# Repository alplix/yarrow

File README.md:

# Yarrow

Open software for Geiger counters: firmware for the FNIRSI GC-03, a BOINC monitor that reads several kinds of counters, and
a desktop app. Together they feed a live, open map of the natural background dose rate, city by city.

**Website:** [yarrow.athena.org.tr](https://yarrow.athena.org.tr) · **Live map:** [bitboinc.athena.org.tr/yarrow.php](https://bitboinc.athena.org.tr/yarrow.php) · **Data by city:** [bitboinc.athena.org.tr/yarrow_history.php](https://bitboinc.athena.org.tr/yarrow_history.php) · **Releases:** [firmware per language and Yarrow Hub](https://github.com/alplix/yarrow/releases)

3D Printed Dock: https://www.crealitycloud.com/tr/model-detail/6adf8eee3737a58cb2d2e141?profileId=6adf8eee3737a58cb2d2e147

## The parts

| | |
|---|---|
| **Firmware** (`src/`) | Open firmware for the FNIRSI GC-03: readable at a glance, measures honestly, logs for years. |
| **BOINC monitor** (`monitor/`) | A small program that reads a counter, cuts its pulses into exact 10-minute bins and sends them to the project as BOINC trickles. |
| **Yarrow Hub** (`hub/`) | A desktop app that works without BOINC: live dose rate, history, statistics, alarms, CSV export. |
| **Website** (`site/`) | The project page, in English and Turkish. |

## Supported counters

| Counter | Connection | Monitor | Hub |
|---|---|---|---|
| FNIRSI GC-03 with the Yarrow firmware | USB serial | yes | yes |
| [Radioactive@Home USB counters](docs/radioactive-at-home.md) (boards 2.01 to 2.60, the kit, and 3.01) | USB HID, nothing to flash | yes | yes |
| GQ GMC-300 / 320 / 500 / 600 | USB serial | yes | yes (live, recorded while connected; no stored history) |

Only raw pulse counts from the tube are accepted, never a rate the counter has smoothed itself. A new counter is one small
driver in `monitor/yarrow_src_*.c`; see [docs/boinc-monitor.md](docs/boinc-monitor.md).

## Join the map

1. Join [bitboinc](https://bitboinc.athena.org.tr) and attach your computer in the BOINC Manager.
2. In your project preferences select the Yarrow monitor and enter your country, city and (if you like) your detector.
3. Plug in the counter and leave the computer on. Only the city is shared, never a more exact place.

## Yarrow Hub

Download [yarrow-hub-windows-x64-setup.exe](https://github.com/alplix/yarrow/releases/latest/download/yarrow-hub-windows-x64-setup.exe).
It shows the live dose rate, keeps the history on your computer, draws statistics, shows nSv/h, µSv/h or µrem/h, rings
alarms at levels you choose and exports CSV. With a GC-03 it also sets the clock, calibrates the tube and installs
firmware. Built with Tauri (Rust and TypeScript); to build it: `cd hub/app && cargo tauri build`.

## What the firmware does

**Radiation**
- Dose rate, counts per minute, dose today, this week and in total
- An averaging window that follows the rate: long and quiet at background, quick when the rate really changes, without leaning high or low
- Tube dead-time correction
- Three alarm levels with fixed thresholds you set yourself, hysteresis, an event log and an alarm that never fires from a handful of counts
- Dose budget, sample test (background against sample), sessions for trips, walks and surveys, a calibration wizard and a two-source dead-time wizard

**Fields**
- Electric and magnetic field readings with trends
- A finder that follows wires and field sources by sound and bars

**Device**
- Battery health, remaining run time, charge cycles, a charging screen
- A log designed for years in the mountains: lossless range-coded samples, power-fail safe, within a few percent of the theoretical minimum size
- Offline emergency guide
- 21 colour themes, pixel-art decoration, a self test
- USB serial protocol for the host tools

## Install the firmware

Download the file for your language from [Releases](https://github.com/alplix/yarrow/releases) and copy it to the device in update mode. The stock bootloader is never touched, so the stock firmware can always be put back the same way. Step by step: [docs/install.md](docs/install.md).

## Build the firmware

Needs `arm-none-eabi-gcc`, GNU make and Python 3 for the build helpers.

    make                 # Turkish, build/yarrow-gc03.bin
    make YLANG=en        # English, build/en/yarrow-gc03.bin
    make release YLANG=en  # copies it to dist/yarrow-gc03-en.bin
    make check           # host tests
    make test            # runs the image in an ARM emulator
    make sim             # renders every screen to build/sim

Details in [docs/building.md](docs/building.md).

## Languages

Every language is its own firmware file, because the fonts take most of the room.

| | | | |
|---|---|---|---|
| `tr` Türkçe | `en` English | `de` Deutsch | `fr` Français |
| `es` Español | `pt` Português (Brasil) | `it` Italiano | `nl` Nederlands |
| `pl` Polski | `ru` Русский | `uk` Українська | `vi` Tiếng Việt |
| `id` Bahasa Indonesia | `zh` 简体中文 | `ja` 日本語 | `ko` 한국어 |

Adding one means copying `src/lang/en.h`, translating it and running `tools/langcheck.py`; a local model can do the first
pass: [docs/translating.md](docs/translating.md).

## Documentation

| | |
|---|---|
| [docs/install.md](docs/install.md) | putting Yarrow on the device and going back |
| [docs/usage.md](docs/usage.md) | keys, screens, alarms, sessions |
| [docs/boinc-monitor.md](docs/boinc-monitor.md) | the BOINC monitor, supported counters, server checks, credit |
| [docs/radioactive-at-home.md](docs/radioactive-at-home.md) | the Radioactive@Home counters: boards, V2.60 schematic, report format |
| [docs/data.md](docs/data.md) | what is sent, how it is checked, where to read the data |
| [docs/calibration.md](docs/calibration.md) | matching the readings to a reference |
| [docs/hardware.md](docs/hardware.md) | pins and memory map of the GC-03 |
| [docs/serial-protocol.md](docs/serial-protocol.md) | the USB command protocol |
| [docs/log-format.md](docs/log-format.md) | how the log is stored and compressed |
| [docs/building.md](docs/building.md) | toolchain, tests, simulator |
| [docs/translating.md](docs/translating.md) | adding a language |
| [docs/bringup.md](docs/bringup.md) | test images for a new board |

## Licence

GPL-3.0, see [LICENSE](LICENSE). The Inter font in `third_party/inter` is under the SIL Open Font License.

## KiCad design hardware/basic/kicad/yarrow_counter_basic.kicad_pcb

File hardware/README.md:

# Yarrow Counter: open hardware

A family of USB Geiger counters designed for the Yarrow network, in three steps from cheap to accurate. Each step is a
board of its own, built and measured before the next one is drawn, so what is learned on the cheap board goes into the
better ones. The boards speak the Yarrow serial protocol ([../docs/serial-protocol.md](../docs/serial-protocol.md)), so
the BOINC monitor and Yarrow Hub read them without new drivers.

Status: design. Nothing here has been built yet.

## What decides the quality of a reading

A Geiger counter measures by counting, so the uncertainty is mostly counting noise: it falls with the square root of the
number of pulses. Everything below serves one of four things.

1. **More pulses for the same dose rate.** A bigger or a second tube. Ten times the pulses is three times less noise.
2. **Every pulse counted exactly.** Pulses are time-stamped by a hardware timer capture (microseconds), not polled, so the
   dead time of the tube can be measured and corrected, and a burst is never lost.
3. **A stable tube voltage.** The count rate of a tube depends on its voltage; a regulated and measured supply keeps the
   sensitivity the same over temperature and battery or USB sag.
4. **Time that does not depend on the computer.** Bins are cut at exact edges. A counter that keeps its own time (RTC, and
   at the top step GPS) does not need the host clock to be right.

## The three steps

| | **Basic** | **Plus** | **Pro** |
|---|---|---|---|
| Idea | the cheapest board that is correct | better tube and voltage control | the best reading one location can get |
| MCU | CH32F203 (as in the GC-03) | CH32F203 | CH32F203 or a larger one, plus ESP32-C3 for Wi-Fi |
| Tube | SBM-20 (the Radioactive@Home tube) | larger or higher-sensitivity tube (footprint for J305 and M4011 class) | two tubes of the same kind |
| High voltage | boost regulated by the firmware from a measured voltage | the same plus a hardware limit | the same, temperature-compensated |
| Pulses | timer capture, microsecond stamps | the same, with pulse width | the same on both tubes, coincidences logged |
| Time | host clock, edges as the monitor does now | RTC with backup cell | GPS pulse-per-second discipline |
| Link | USB (CDC serial) | USB | USB and Wi-Fi (headless station) |
| Extras | LED, buzzer | small display, temperature sensor | pressure and humidity, SD log |
| Aim | a first kit anyone can solder; the reference for the protocol | trustworthy long-term station in a house | reference station; cross-checks the cheaper ones |

Open points for Plus and Pro are decided by what the Basic board shows: how the tube really behaves with the boost
converter, how much noise reaches the pulse input, how large the temperature drift is.

## Shared design rules

- **Safety.** The tube supply is about 400 V at a few microamps. The high-voltage part sits in one marked corner of the
  board with creepage clearance, nothing with high voltage is reachable from the outside, and the first prototypes are
  tested with a high-impedance probe and a current-limited source.
- **No bootloader lock-in.** Every board has a SWD header and a boot-select jumper, so a bad firmware can always be
  replaced (unlike the GC-03).
- **Only raw counts.** The firmware reports pulses and their time stamps; dose rate is calculated on the host from the
  sensitivity written in the device, so a better calibration can be applied later to old data.
- **Same protocol.** The identity and calibration commands report the board, the tube and its sensitivity and dead time.
- **Openness.** Schematic and layout in KiCad, firmware in this repository, licence CERN-OHL-S for the hardware and
  GPL-3.0 for the firmware.

## Rounds

1. **Basic, first spin.** Schematic, small two-layer board, order five. Measure: tube voltage and ripple, pulse shape,
   count rate against a reference counter (the GC-03 and a Radioactive@Home counter side by side), temperature drift.
2. **Basic, second spin** with what the first one showed, then published as a kit.
3. **Plus.** Closed-loop supply, RTC, display, the better tube; compared against Basic and the reference counters.
4. **Pro.** Two tubes, GPS, Wi-Fi; becomes the station that checks the cheaper ones.

Each round ends with a measurement report in `hardware/reports/` (the numbers, not just whether it works).

## What is here

[basic/](basic/DESIGN.md): the design of the Basic board with the calculations (`hv_calc.py`), the bill of materials and the
net list the schematic is drawn from. Next: the KiCad schematic and layout, and the firmware port.

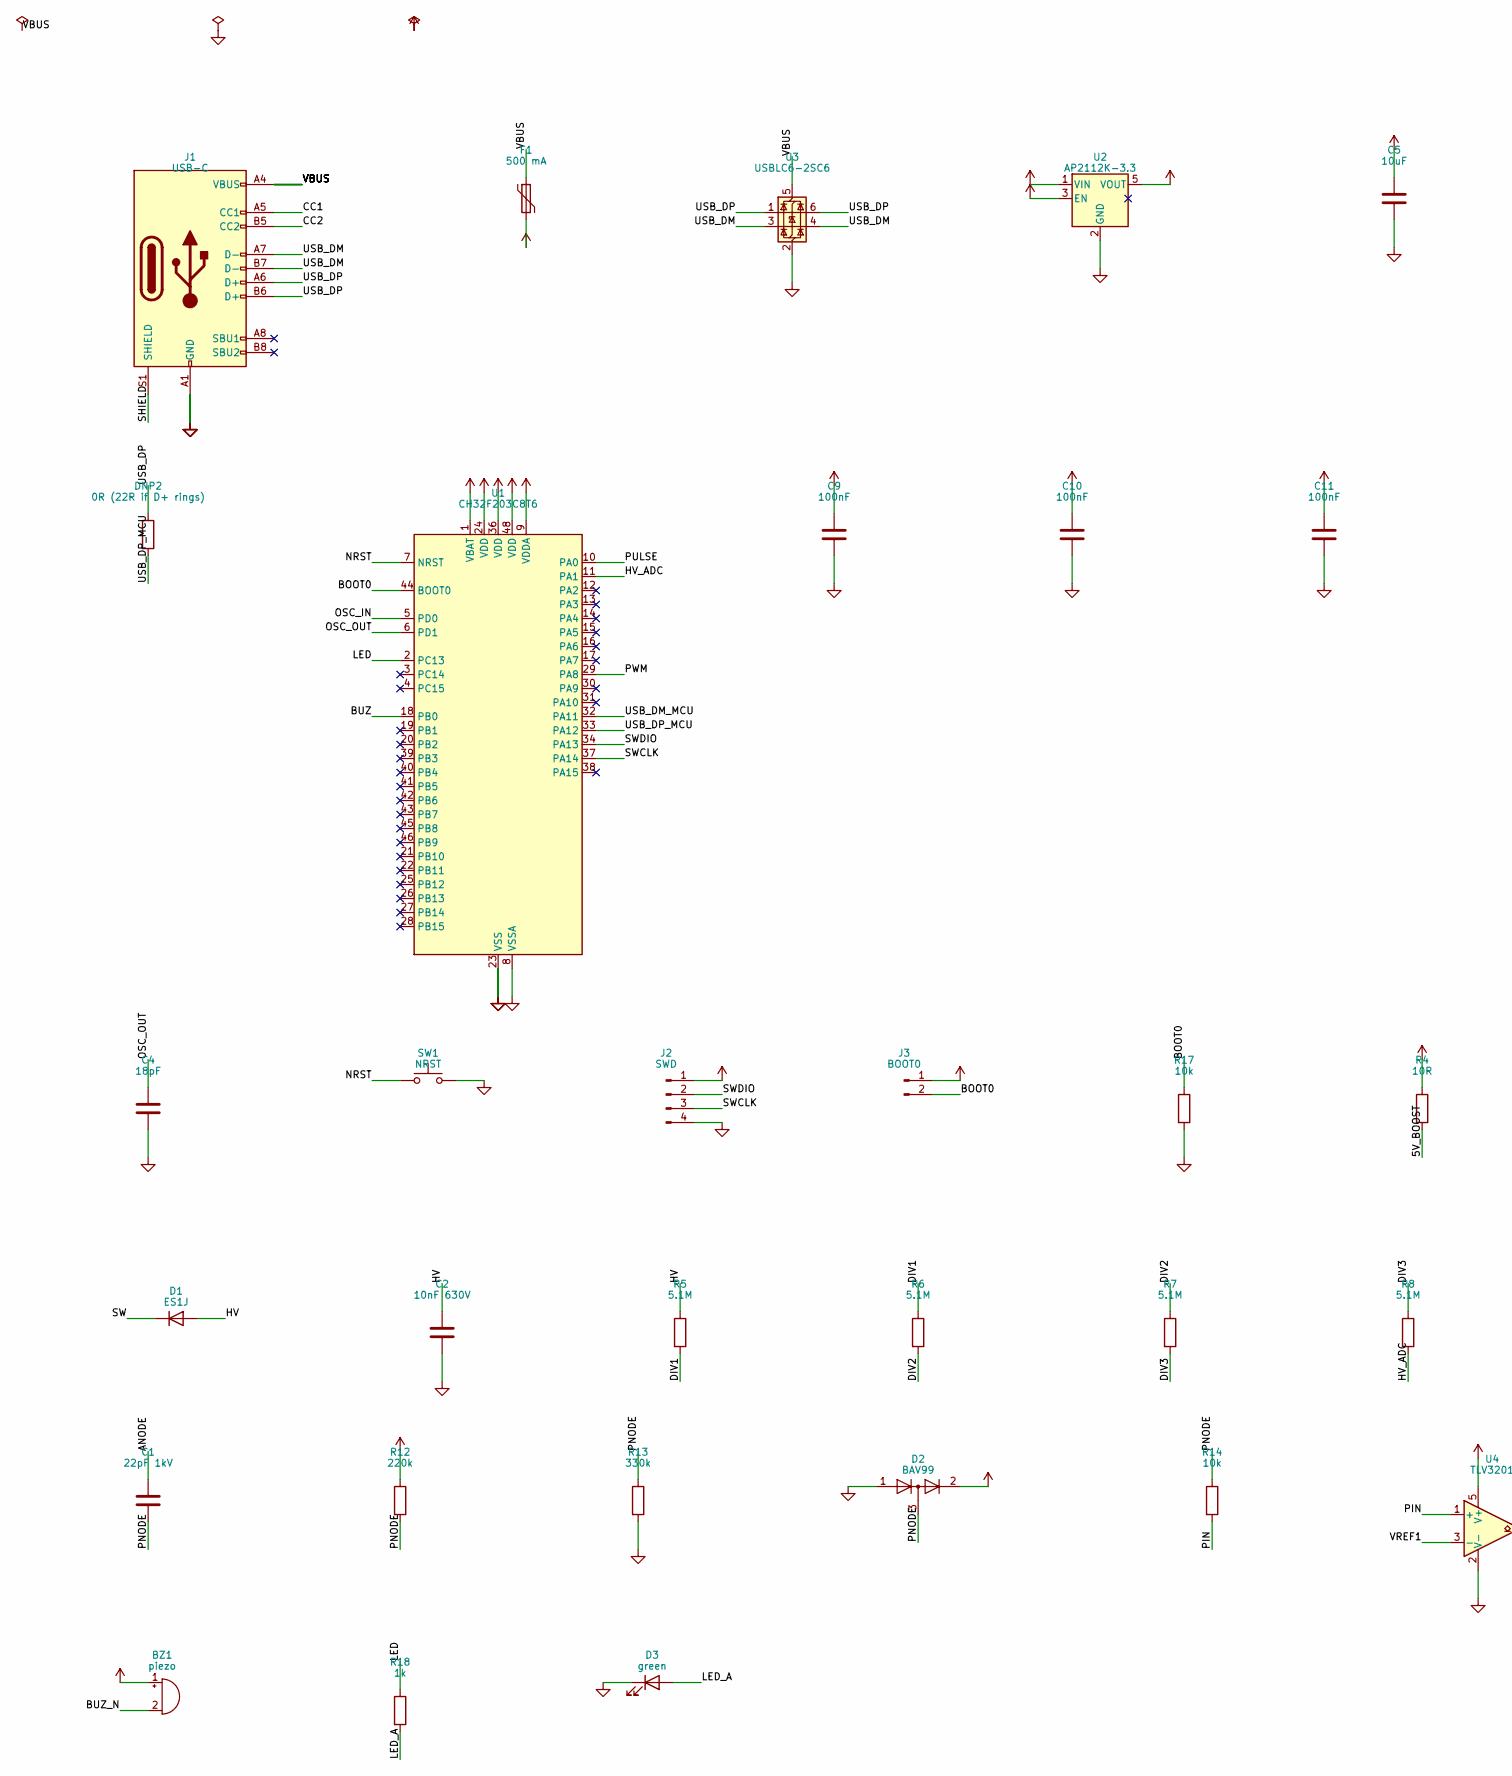
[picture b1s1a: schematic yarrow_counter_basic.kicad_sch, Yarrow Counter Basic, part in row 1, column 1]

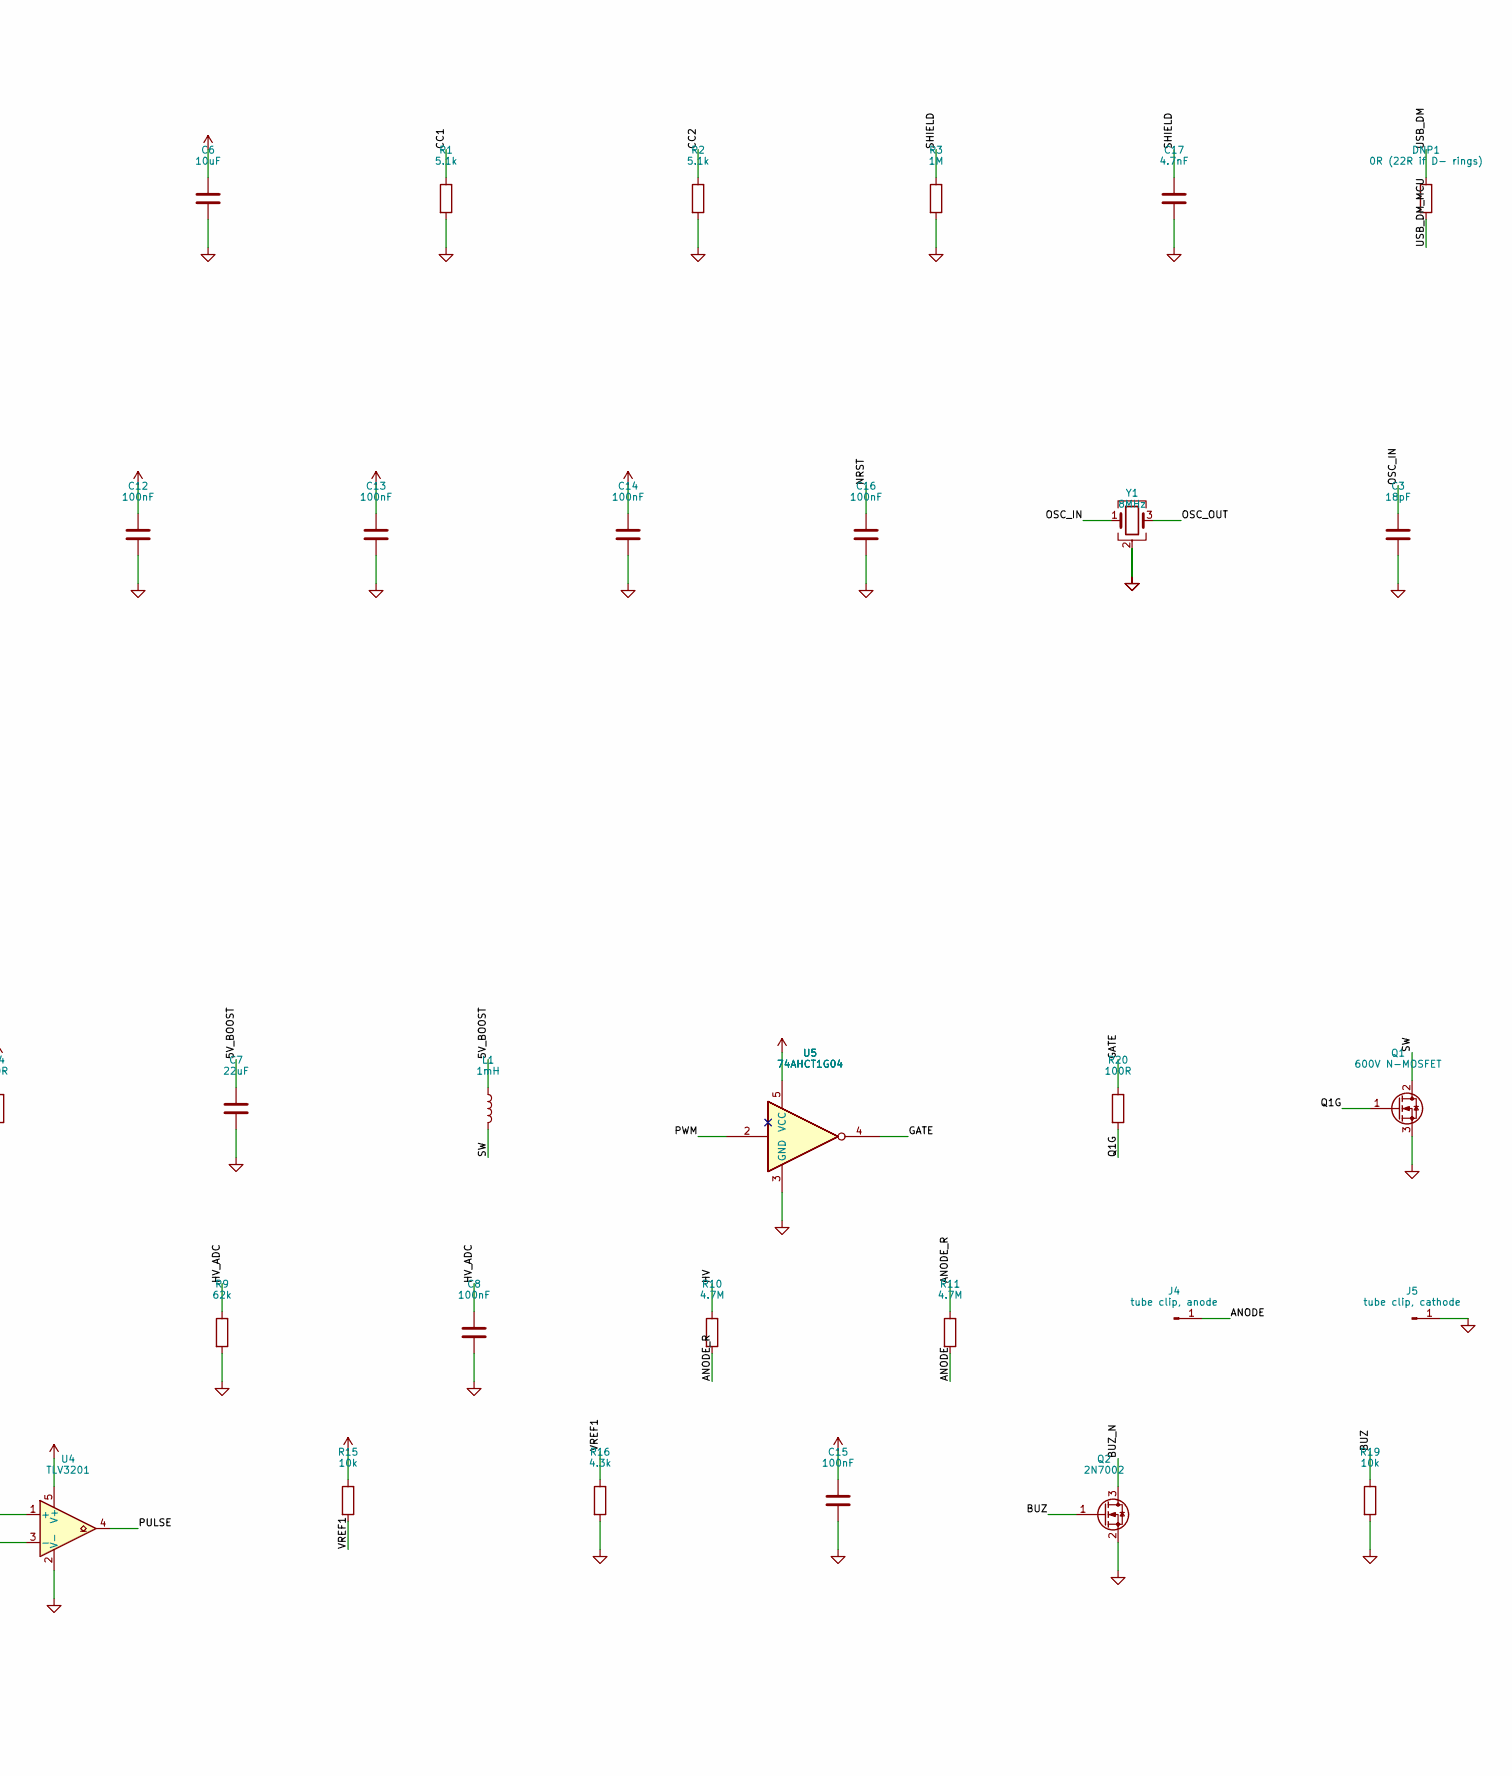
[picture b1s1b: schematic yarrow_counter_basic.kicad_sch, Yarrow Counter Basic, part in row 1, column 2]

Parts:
BZ1: piezo; Buzzer_12x9.5RM7.6
C1: 22pF 1kV; C_1812_4532Metric
C2: 10nF 630V; C_1812_4532Metric
C3, C4: 18pF; C_0402_1005Metric
C5, C6: 10uF; C_0805_2012Metric
C7: 22uF; C_0805_2012Metric
C8, C9, C10, C11, C12, C13, C14, C15, C16: 100nF; C_0402_1005Metric
C17: 4.7nF; C_0402_1005Metric
D1: ES1J; D_SMA
D2: BAV99; SOT-23
D3: green; LED_0805_2012Metric
DNP1: 0R (22R if D- rings); R_0402_1005Metric
DNP2: 0R (22R if D+ rings); R_0402_1005Metric
F1: 500 mA; Fuse_1206_3216Metric
J1: USB-C; USB_C_Receptacle_G-Switch_GT-USB-7010ASV
J2: SWD; PinHeader_1x04_P2.54mm_Vertical
J3: BOOT0; PinHeader_1x02_P2.54mm_Vertical
J4: tube clip, anode; TestPoint_THTPad_D3.0mm_Drill1.5mm
J5: tube clip, cathode; TestPoint_THTPad_D3.0mm_Drill1.5mm
L1: 1mH; L_7.3x7.3_H4.5
Q1: 600V N-MOSFET; TO-252-3_TabPin2
Q2: 2N7002; SOT-23
R1, R2: 5.1k; R_0402_1005Metric
R3: 1M; R_0402_1005Metric
R4: 10R; R_0603_1608Metric
R5, R6, R7, R8: 5.1M; R_1206_3216Metric
R9: 62k; R_0402_1005Metric
R10, R11: 4.7M; R_1206_3216Metric
R12: 220k; R_0402_1005Metric
R13: 330k; R_0402_1005Metric
R14, R15, R17, R19: 10k; R_0402_1005Metric
R16: 4.3k; R_0402_1005Metric
R18: 1k; R_0402_1005Metric
R20: 100R; R_0402_1005Metric
SW1: NRST; SW_SPST_B3S-1000
U1: CH32F203C8T6; LQFP-48_7x7mm_P0.5mm
U2: AP2112K-3.3; SOT-23-5
U3: USBLC6-2SC6; SOT-23-6
U4: TLV3201; SOT-23-5
U5: 74AHCT1G04; SOT-23-5
Y1: 8MHz; Crystal_SMD_3225-4Pin_3.2x2.5mm

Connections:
5V_BOOST: C7.1, L1.1, R4.2
+3V3: C6.1, C9.1, C10.1, C11.1, C12.1, C13.1, C14.1, C15.1, D2.2 (A), J2.1, J3.1, R12.1, R15.1, U1.1 (VBAT), U1.9 (VDDA), U1.24 (VDD), U1.36 (VDD), U1.48 (VDD), U2.5 (VOUT), U4.5 (V+)
+5V: BZ1.1 (+), C5.1, F1.2, R4.1, U2.1 (VIN), U2.3 (EN), U5.5 (VCC)
ANODE: C1.1, J4.1, R11.2
ANODE_R: R10.2, R11.1
BOOT0: J3.2, R17.1, U1.44 (BOOT0)
BUZ: Q2.1 (G), R19.1, U1.18 (PB0)
BUZ_N: BZ1.2 (-), Q2.3 (D)
CC1: J1.A5 (CC1), R1.1
CC2: J1.B5 (CC2), R2.1
DIV1: R5.2, R6.1
DIV2: R6.2, R7.1
DIV3: R7.2, R8.1
GATE: R20.1, U5.4
GND: C2.2, C3.2, C4.2, C5.2, C6.2, C7.2, C8.2, C9.2, C10.2, C11.2, C12.2, C13.2, C14.2, C15.2, C16.2, C17.2, D2.1 (K), D3.1 (K), J1.A1 (GND), J1.A12 (GND), J1.B1 (GND), J1.B12 (GND), J2.4, J5.1, Q1.3 (S), Q2.2 (S), R1.2, R2.2, R3.2, R9.2, R13.2, R16.2, R17.2, R19.2, SW1.2, U1.8 (VSSA), U1.23 (VSS), U1.35 (VSS), U1.47 (VSS), U2.2 (GND), U3.2 (GND), U4.2 (V-), U5.3 (GND), Y1.2 (G), Y1.4 (G)
HV: C2.1, D1.2 (A), R5.1, R10.1
HV_ADC: C8.1, R8.2, R9.1, U1.11 (PA1)
LED: R18.1, U1.2 (PC13)
LED_A: D3.2 (A), R18.2
NRST: C16.1, SW1.1, U1.7 (NRST)
OSC_IN: C3.1, U1.5 (PD0), Y1.1
OSC_OUT: C4.1, U1.6 (PD1), Y1.3
PIN: R14.2, U4.1 (+)
PNODE: C1.2, D2.3 (K), R12.2, R13.1, R14.1
PULSE: U1.10 (PA0), U4.4
PWM: U1.29 (PA8), U5.2
Q1G: Q1.1 (G), R20.2
SHIELD: C17.1, J1.S1 (SHIELD), R3.1
SW: D1.1 (K), L1.2, Q1.2 (D)
SWCLK: J2.3, U1.37 (PA14)
SWDIO: J2.2, U1.34 (PA13)
USB_DM: DNP1.1, J1.A7 (D-), J1.B7 (D-), U3.3 (I/O2), U3.4 (I/O2)
USB_DM_MCU: DNP1.2, U1.32 (PA11)
USB_DP: DNP2.1, J1.A6 (D+), J1.B6 (D+), U3.1 (I/O1), U3.6 (I/O1)
USB_DP_MCU: DNP2.2, U1.33 (PA12)
VBUS: F1.1, J1.A4 (VBUS), J1.A9 (VBUS), J1.B4 (VBUS), J1.B9 (VBUS), U3.5 (VBUS)
VREF1: R15.2, R16.1, U4.3 (-)

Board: 2 copper layers, 62 parts (0 on the bottom side), 37 nets, no tracks yet.

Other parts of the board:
H1, H2, H3: M2.5; MountingHole_2.7mm_M2.5

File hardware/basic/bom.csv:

Ref,Qty,Value,Package,Description,Suggested part
U1,1,CH32F203C8T6,LQFP-48,MCU with USB,WCH CH32F203C8T6
U2,1,3.3 V LDO,SOT-23-5,600 mA low-dropout regulator,Diodes AP2112K-3.3
U3,1,USBLC6-2SC6,SOT-23-6,USB ESD protection,ST USBLC6-2SC6
U4,1,TLV3201,SOT-23-5,40 ns comparator for the pulse input,TI TLV3201AIDBVR
U5,1,74AHCT1G04,SOT-23-5,inverter with TTL input levels; 5 V gate drive,Nexperia 74AHCT1G04GW
Q1,1,600 V N-MOSFET,SOT-223 or DPAK,boost switch; check Rds(on) at Vgs = 5 V,onsemi FQD1N60C or equivalent
Q2,1,2N7002,SOT-23,buzzer driver,any 2N7002
D1,1,ES1J,SMA,600 V 35 ns boost diode,Diodes ES1J
D2,1,BAV99,SOT-23,pulse input clamp (dual series diode),any BAV99
D3,1,LED,0805,pulse indicator (green),any
L1,1,1 mH,>= 100 mA saturation,boost inductor shielded SMD,e.g. Bourns SDR0805-102KL or larger
F1,1,500 mA,1206,USB polyfuse,any 1206 resettable fuse
J1,1,USB-C receptacle,16-pin,power and data (sink only),any 16-pin USB-C
J2,1,SWD header,1x4 2.54 mm,3V3 SWDIO SWCLK GND,pin header
J3,1,BOOT0 jumper,1x2 2.54 mm,boot-select,pin header
SW1,1,NRST,SMD 3x4 mm,reset button,any tact switch
Y1,1,8 MHz,3225,crystal 18 pF load,any
BZ1,1,piezo,12 mm,passive transducer about 4 kHz,any passive piezo
TUBE,2,tube clip,for 11 mm tube,holds the SBM-20 / STS-5 on the board (about 108 mm apart; anode clip at the high-voltage end),any metal tube clip
C1,1,22 pF 1 kV,1206 C0G,pulse coupling capacitor,Murata GRM31A5C3A220JW01 or equivalent
C2,1,10 nF 630 V,1206 or 1210 X7R,HV output capacitor,any 630 V
C3-C4,2,18 pF,0402,crystal load,any C0G
C5-C6,2,10 uF,0805,LDO in and out,any
C7,1,22 uF,0805 or 1206,boost supply reservoir,any
C8,1,100 nF,0402,HV divider filter at the ADC pin,any
C9-C16,8,100 nF,0402,decoupling,any
C17,1,4.7 nF,0402,USB shield to ground,any
R1-R2,2,5.1 k,0402,USB-C CC pull-downs,any
R3,1,1 M,0402,USB shield to ground,any
R4,1,10 R,0603,boost supply filter,any
R5-R8,4,5.1 M,1206,HV divider top (each sees about 100 V),any 1206 1 % (rated for 200 V)
R9,1,62 k,0402,HV divider bottom,any 1 %
R10-R11,2,4.7 M,1206,tube anode resistors,any 1206 5 %
R12,1,220 k,0402,pulse node pull-up,any
R13,1,330 k,0402,pulse node pull-down,any
R14,1,10 k,0402,pulse node series (protects the comparator input),any
R15,1,10 k,0402,comparator reference divider top (3.3 V),any
R16,1,4.3 k,0402,comparator reference divider bottom (gives 0.99 V),any
R17,1,10 k,0402,BOOT0 pull-down,any
R18,1,1 k,0402,LED series,any
R19,1,10 k,0402,Q2 gate pull-down,any
R20,1,100 R,0402,gate resistor of Q1,any
R21-R22,2,0 R,0402,USB series positions (DNP1 and DNP2 in the schematic): 0 ohm links in the first spin; 22 ohm if D+ and D- ring,any
